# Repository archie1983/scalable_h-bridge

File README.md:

So this is a simple, scalable H-bridge, that I made on my own inspired by a design of an H-bridge in some chinese toy car.

Nothing special really- just a dual motor h-bridge. Circuits like this can be bought off the shelf on Ebay, Amazon and many other places, but mine can be customised. 
So for instance I needed 4.5A of current to drive my little DC130 motors at 7.5V, but I could only find 2A designs on Ebay for a reasonable price, so I made my own. And if I ever want 6A for instance, all I need to do, is add 8 more transistors to the output stage: 4x SS8050 and 4x SS8550.

Other design ideas for future include:
1) adding reverse diodes to the output transistors to be able to drive bigger motors.
2) Also it will be nice to incorporate a microcontroller on the same board at some point in the future.
3) Ballast resistors may need to be added to each of the output stage transistors to guarantee that they channel equal amounts of current.

The project was designed in KiCad 5.0.1.

Please feel free to use and improve it.

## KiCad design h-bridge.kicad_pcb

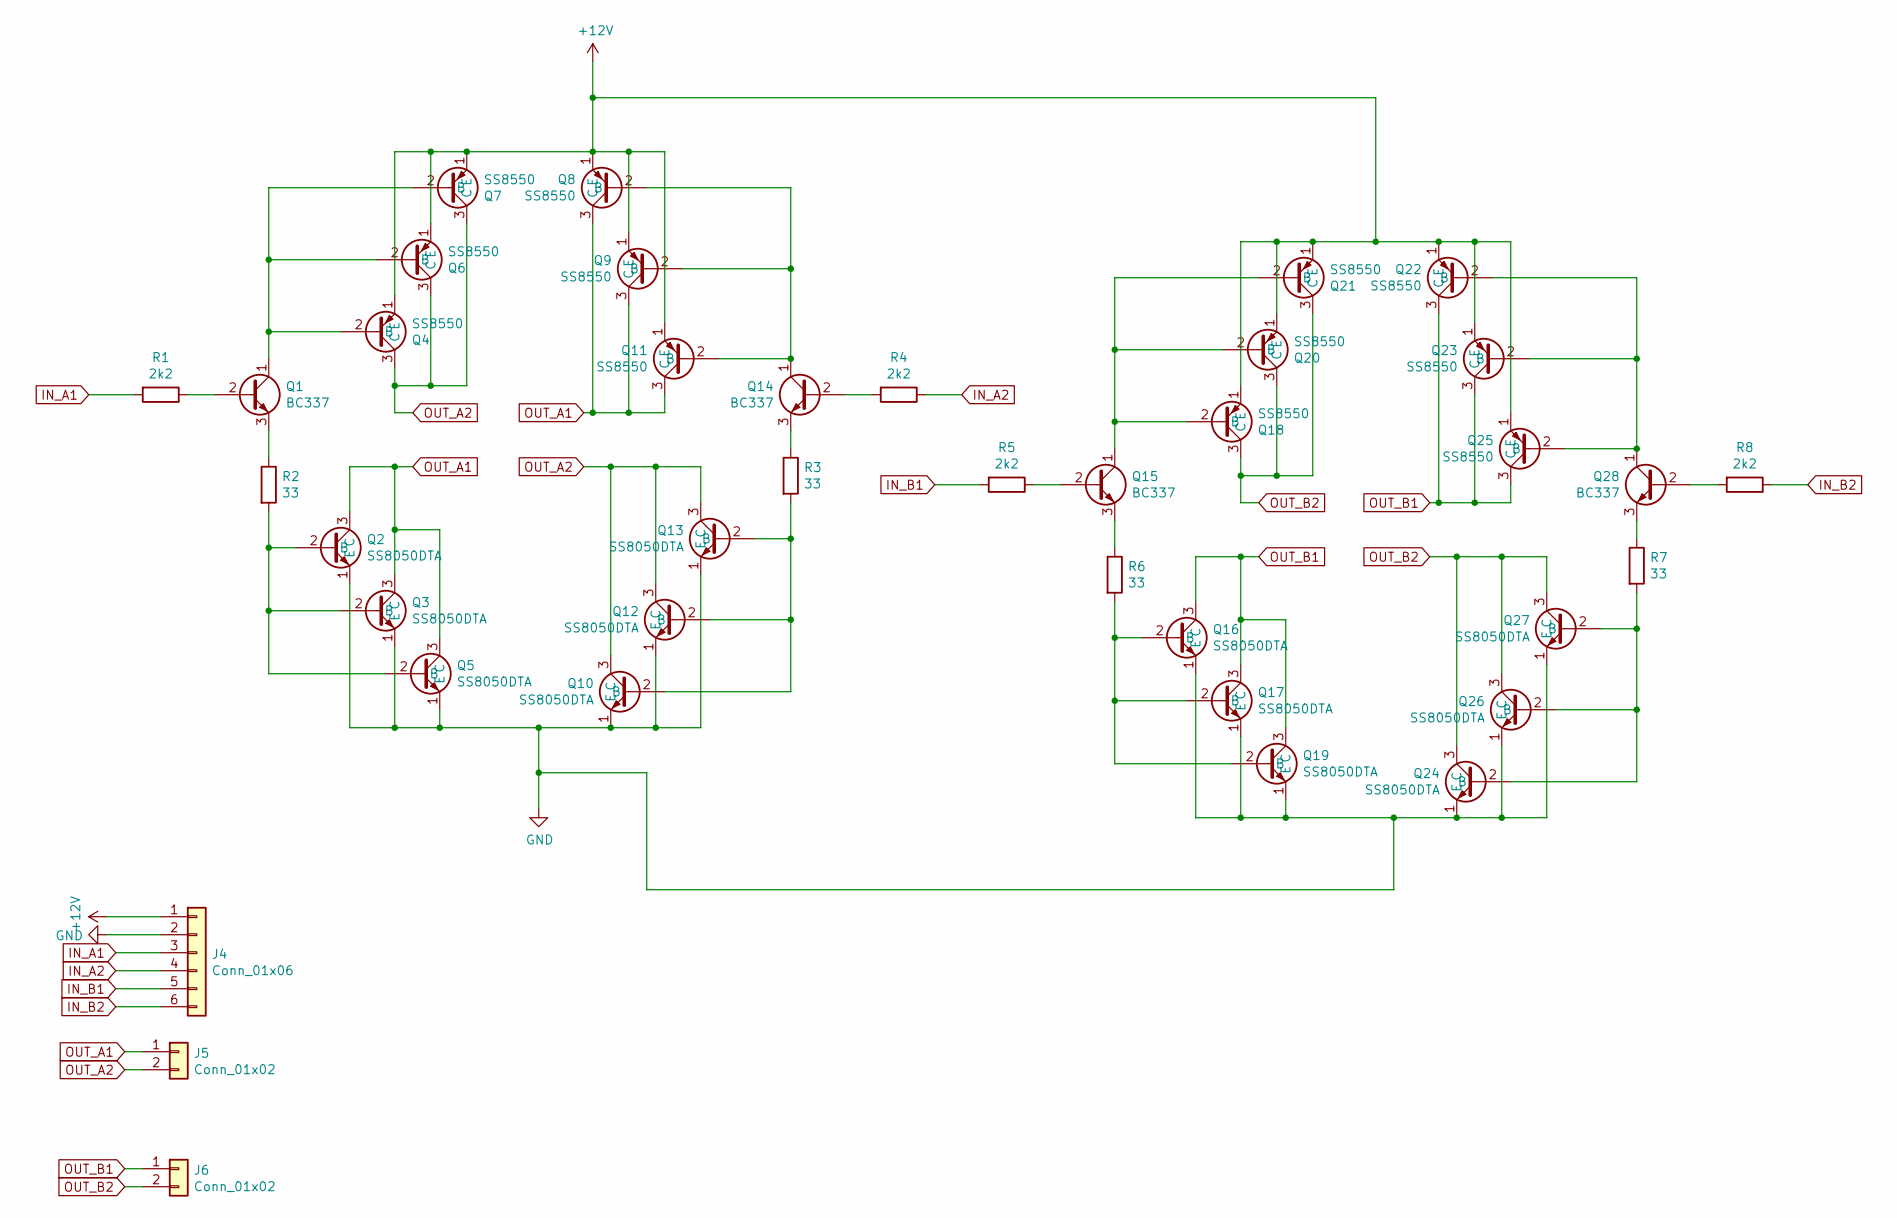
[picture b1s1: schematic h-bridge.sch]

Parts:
J4: Conn_01x06; PinHeader_1x06_P2.54mm_Vertical
J5, J6: Conn_01x02; PinHeader_1x02_P2.54mm_Vertical
Q1, Q14, Q15, Q28: BC337; TO-92_Inline_Wide
Q2, Q3, Q5, Q10, Q12, Q13, Q16, Q17, Q19, Q24, Q26, Q27: SS8050DTA; TO-92_Inline_Wide
Q4, Q6, Q7, Q8, Q9, Q11, Q18, Q20, Q21, Q22, Q23, Q25: SS8550; TO-92_Inline_Wide
R1, R4, R5, R8: 2k2; R_Axial_DIN0207_L6.3mm_D2.5mm_P5.08mm_Vertical
R2, R3, R6, R7: 33; R_Axial_DIN0414_L11.9mm_D4.5mm_P5.08mm_Vertical

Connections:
+12V: J4.1, Q4.1 (E), Q6.1 (E), Q7.1 (E), Q8.1 (E), Q9.1 (E), Q11.1 (E), Q18.1 (E), Q20.1 (E), Q21.1 (E), Q22.1 (E), Q23.1 (E), Q25.1 (E)
GND: J4.2, Q2.1 (E), Q3.1 (E), Q5.1 (E), Q10.1 (E), Q12.1 (E), Q13.1 (E), Q16.1 (E), Q17.1 (E), Q19.1 (E), Q24.1 (E), Q26.1 (E), Q27.1 (E)
IN_A1: J4.3, R1.2
IN_A2: J4.4, R4.1
IN_B1: J4.5, R5.2
IN_B2: J4.6, R8.1
unnamed: Q1.1 (C), Q4.2 (B), Q6.2 (B), Q7.2 (B)
unnamed: Q1.2 (B), R1.1
unnamed: Q1.3 (E), R2.1
unnamed: Q2.2 (B), Q3.2 (B), Q5.2 (B), R2.2
unnamed: Q10.2 (B), Q12.2 (B), Q13.2 (B), R3.2
unnamed: Q8.2 (B), Q9.2 (B), Q11.2 (B), Q14.1 (C)
unnamed: Q14.2 (B), R4.2
unnamed: Q14.3 (E), R3.1
unnamed: Q15.1 (C), Q18.2 (B), Q20.2 (B), Q21.2 (B)
unnamed: Q15.2 (B), R5.1
unnamed: Q15.3 (E), R6.1
unnamed: Q16.2 (B), Q17.2 (B), Q19.2 (B), R6.2
unnamed: Q22.2 (B), Q23.2 (B), Q25.2 (B), Q28.1 (C)
unnamed: Q24.2 (B), Q26.2 (B), Q27.2 (B), R7.2
unnamed: Q28.2 (B), R8.2
unnamed: Q28.3 (E), R7.1
OUT_A1: J5.1, Q2.3 (C), Q3.3 (C), Q5.3 (C), Q8.3 (C), Q9.3 (C), Q11.3 (C)
OUT_A2: J5.2, Q4.3 (C), Q6.3 (C), Q7.3 (C), Q10.3 (C), Q12.3 (C), Q13.3 (C)
OUT_B1: J6.1, Q16.3 (C), Q17.3 (C), Q19.3 (C), Q22.3 (C), Q23.3 (C), Q25.3 (C)
OUT_B2: J6.2, Q18.3 (C), Q20.3 (C), Q21.3 (C), Q24.3 (C), Q26.3 (C), Q27.3 (C)

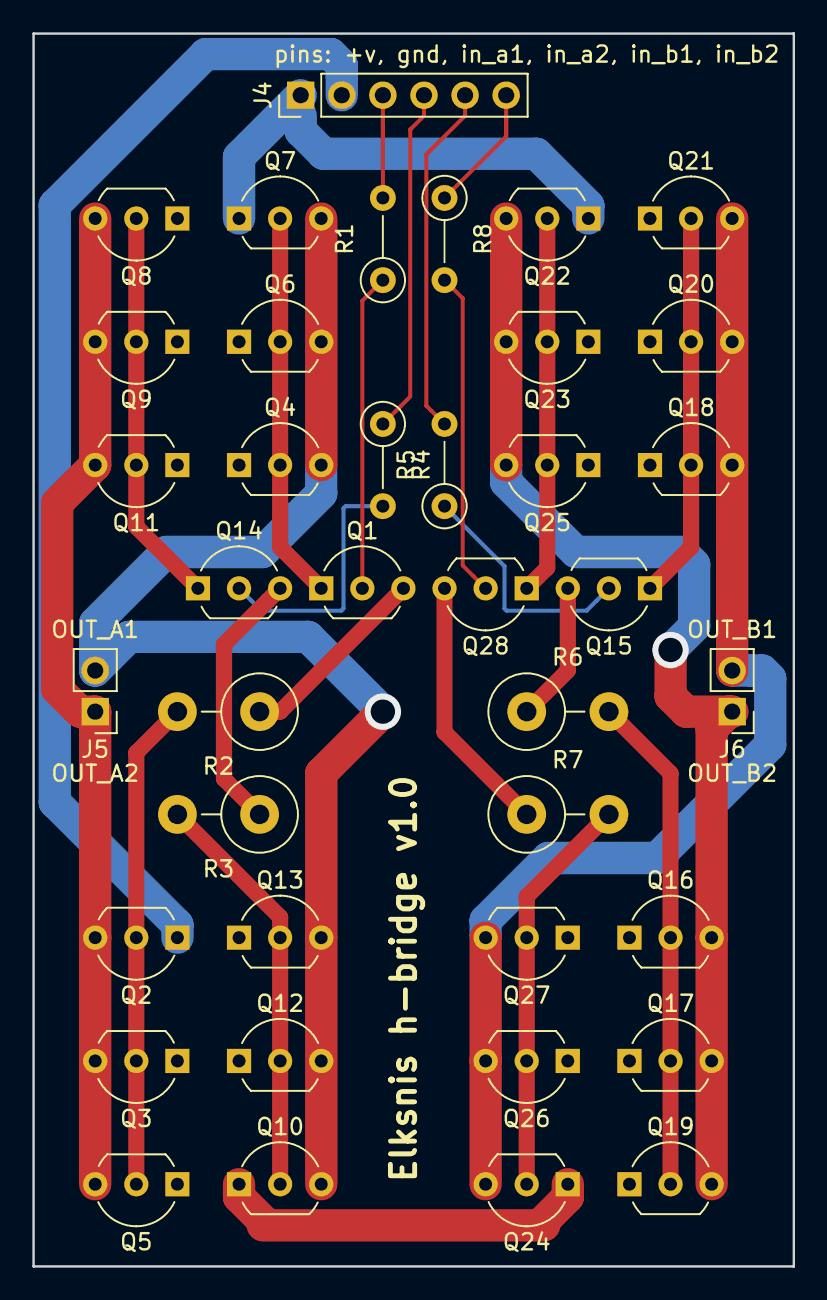
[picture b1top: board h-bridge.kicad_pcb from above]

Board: 2 copper layers, 47.0 x 76.2 mm, 39 parts (0 on the bottom side), 26 nets.

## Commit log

2018-11-15 First commit of my h-bridge project. All ready for first prototype. Gerbers and drill files were sent to JLCPCB and boards manufactured.
2018-11-15 Added README.md
2018-11-15 Added info about KiCad
